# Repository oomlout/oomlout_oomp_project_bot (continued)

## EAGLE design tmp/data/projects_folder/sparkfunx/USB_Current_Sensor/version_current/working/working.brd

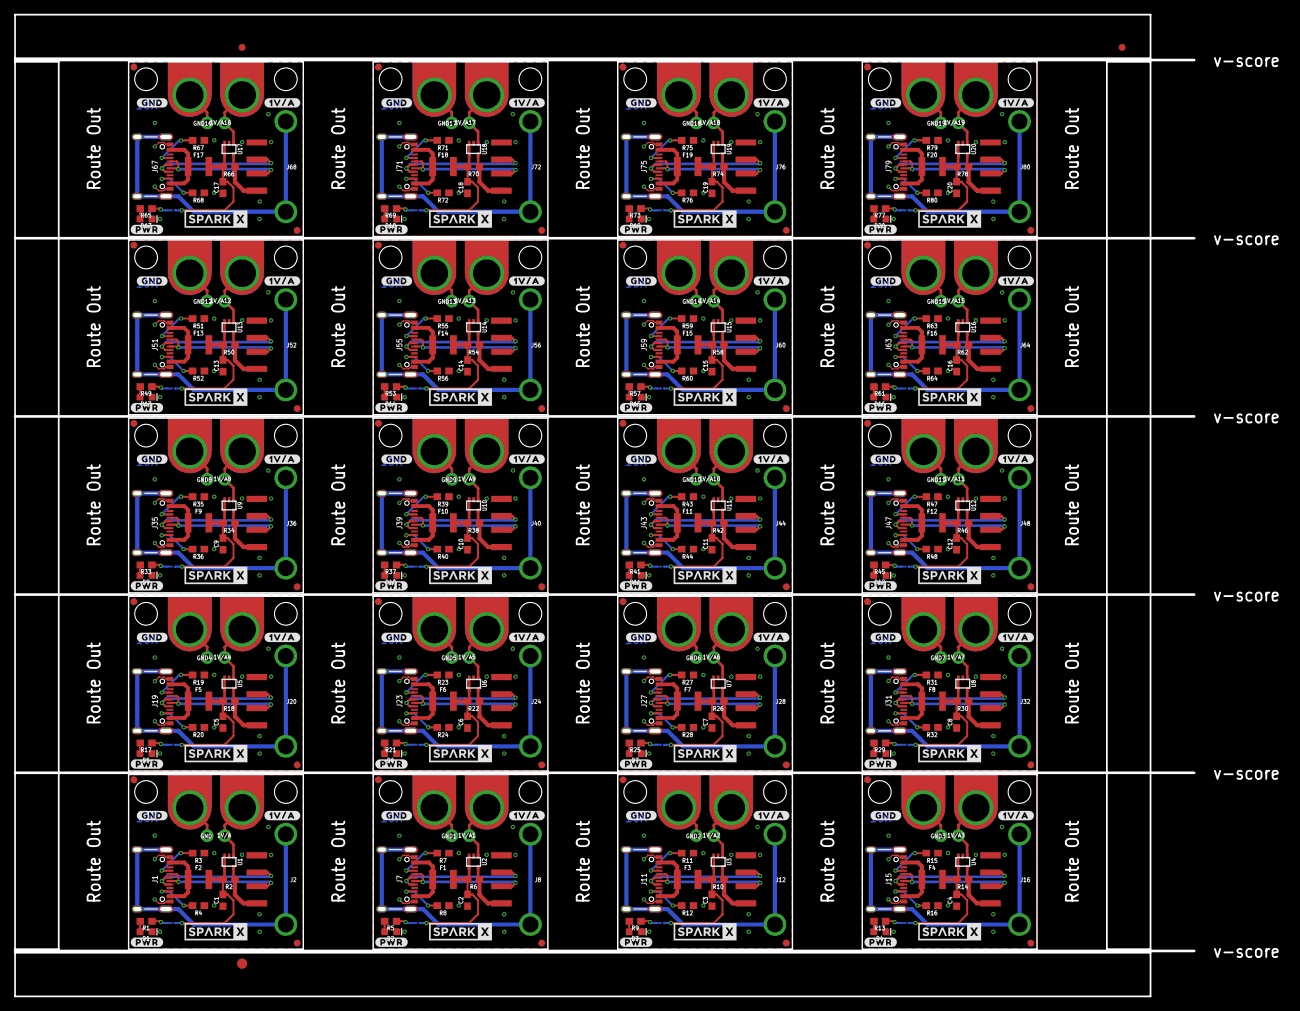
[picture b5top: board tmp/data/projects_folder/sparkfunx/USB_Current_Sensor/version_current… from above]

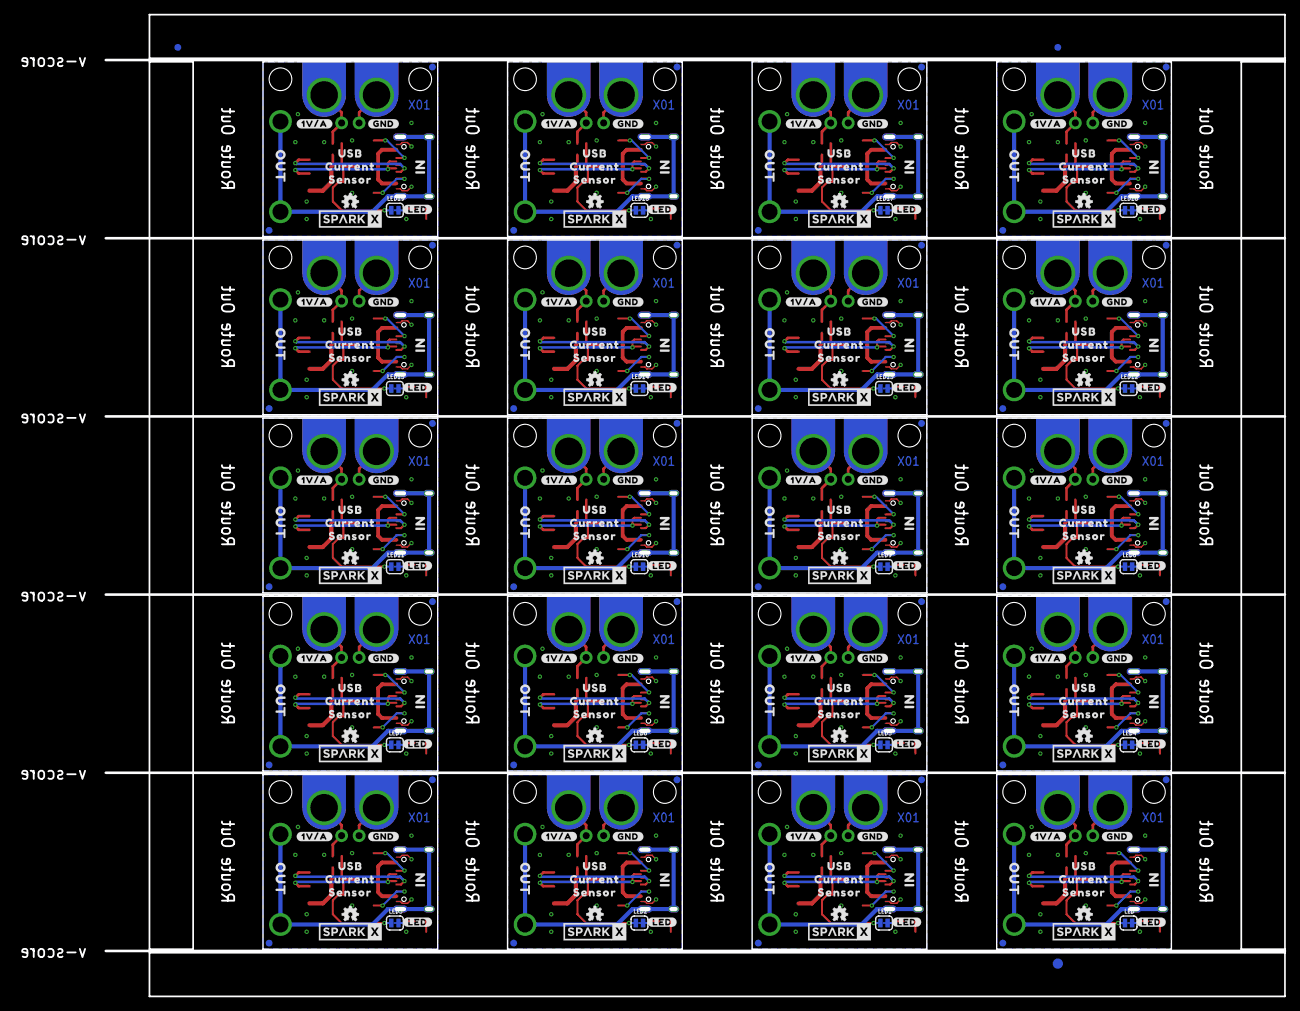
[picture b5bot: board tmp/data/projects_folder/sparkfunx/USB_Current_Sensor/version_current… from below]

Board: 2 copper layers, 171.4 x 142.7 mm, 706 parts (263 on the bottom side), 240 nets.

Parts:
1V/A, 1V/A1, 1V/A2, 1V/A3, 1V/A4, 1V/A5, 1V/A6, 1V/A7, 1V/A8, 1V/A9, 1V/A10, 1V/A11, 1V/A12, 1V/A13, 1V/A14, 1V/A15, 1V/A16, 1V/A17, 1V/A18, 1V/A19: 1X01_NO_SILK
C1, C2, C3, C4, C5, C6, C7, C8, C9, C10, C11, C12, C13, C14, C15, C16, C17, C18, C19, C20: 0.1uF; 0603
D1, D2, D3, D4, D5, D6, D7, D8, D9, D10, D11, D12, D13, D14, D15, D16, D17, D18, D19, D20: RED; LED-0603
E$1, E$2, E$3, E$4: FIDUCIAL-1X2
E$5, E$6: FIDUCIAL-1.5X3
F1, F2, F3, F4, F5, F6, F7, F8, F9, F10, F11, F12, F13, F14, F15, F16, F17, F18, F19, F20: 6V/2A; 1210
GND, GND1, GND2, GND3, GND4, GND5, GND6, GND7, GND8, GND9, GND10, GND11, GND12, GND13, GND14, GND15, GND16, GND17, GND18, GND19: 1X01_NO_SILK
J1, J7, J11, J15, J19, J23, J27, J31, J35, J39, J43, J47, J51, J55, J59, J63, J67, J71, J75, J79: USB-C-16P_4LAYER-PADS
J2, J8, J12, J16, J20, J24, J28, J32, J36, J40, J44, J48, J52, J56, J60, J64, J68, J72, J76, J80: USB_A_FEMALE; USB-A-S-NOSILK-FEMALE
J3, J4, J5, J6, J9, J10, J13, J14, J17, J18, J21, J22, J25, J26, J29, J30, J33, J34, J37, J38, J41, J42, J45, J46, J49, J50, J53, J54, J57, J58, J61, J62, J65, J66, J69, J70, J73, J74, J77, J78: TAB_GATOR_MINI
JP1, JP2, JP5, JP6, JP9, JP10, JP11, JP12, JP15, JP16, JP17, JP18, JP21, JP22, JP23, JP24, JP27, JP28, JP29, JP30, JP33, JP34, JP35, JP36, JP39, JP40, JP41, JP42, JP45, JP46, JP47, JP48, JP51, JP52, JP53, JP54, JP57, JP58, JP59, JP60, JP63, JP64, JP65, JP66, JP69, JP70, JP71, JP72, JP75, JP76, JP77, JP78, JP81, JP82, JP83, JP84, JP87, JP88, JP89, JP90, JP93, JP94, JP95, JP96, JP99, JP100, JP101, JP102, JP105, JP106, JP107, JP108, JP111, JP112, JP113, JP114, JP117, JP118, JP119, JP120: FIDUCIAL1X2; FIDUCIAL-1X2
JP3, JP4, JP7, JP8, JP13, JP14, JP19, JP20, JP25, JP26, JP31, JP32, JP37, JP38, JP43, JP44, JP49, JP50, JP55, JP56, JP61, JP62, JP67, JP68, JP73, JP74, JP79, JP80, JP85, JP86, JP91, JP92, JP97, JP98, JP103, JP104, JP109, JP110, JP115, JP116: STAND-OFF
LED, LED1, LED2, LED3, LED4, LED5, LED6, LED7, LED8, LED9, LED10, LED11, LED12, LED13, LED14, LED15, LED16, LED17, LED18, LED19: SMT-JUMPER_2_NC_TRACE_SILK
LOGO1, LOGO2, LOGO3, LOGO4, LOGO5, LOGO6, LOGO7, LOGO8, LOGO9, LOGO10, LOGO11, LOGO12, LOGO13, LOGO14, LOGO15, LOGO16, LOGO17, LOGO18, LOGO19, LOGO20: OSHW-LOGOMINI; OSHW-LOGO-MINI
R1, R5, R9, R13, R17, R21, R25, R29, R33, R37, R41, R45, R49, R53, R57, R61, R65, R69, R73, R77: 2.2k; 0603
R2, R6, R10, R14, R18, R22, R26, R30, R34, R38, R42, R46, R50, R54, R58, R62, R66, R70, R74, R78: 0.05; 0603
R3, R4, R7, R8, R11, R12, R15, R16, R19, R20, R23, R24, R27, R28, R31, R32, R35, R36, R39, R40, R43, R44, R47, R48, R51, R52, R55, R56, R59, R60, R63, R64, R67, R68, R71, R72, R75, R76, R79, R80: 5.1k; 0603
U1, U2, U3, U4, U5, U6, U7, U8, U9, U10, U11, U12, U13, U14, U15, U16, U17, U18, U19, U20: INA290A1(20V/V); SC70
U$1, U$2, U$12, U$17, U$27, U$30, U$40, U$43, U$53, U$56, U$66, U$69, U$79, U$82, U$92, U$95, U$105, U$108, U$118, U$121, U$131, U$134, U$144, U$147, U$157, U$160, U$170, U$173, U$183, U$186, U$196, U$199, U$209, U$212, U$222, U$225, U$235, U$238, U$248, U$251: SPARKX-LOGO4; SPARKX-MEDIUM
U$3, U$4, U$18, U$19, U$31, U$32, U$44, U$45, U$57, U$58, U$70, U$71, U$83, U$84, U$96, U$97, U$109, U$110, U$122, U$123, U$135, U$136, U$148, U$149, U$161, U$162, U$174, U$175, U$187, U$188, U$200, U$201, U$213, U$214, U$226, U$227, U$239, U$240, U$252, U$253: #GND#0
U$5, U$6, U$20, U$21, U$33, U$34, U$46, U$47, U$59, U$60, U$72, U$73, U$85, U$86, U$98, U$99, U$111, U$112, U$124, U$125, U$137, U$138, U$150, U$151, U$163, U$164, U$176, U$177, U$189, U$190, U$202, U$203, U$215, U$216, U$228, U$229, U$241, U$242, U$254, U$255: #1V#A#0
U$7, U$22, U$35, U$48, U$61, U$74, U$87, U$100, U$113, U$126, U$139, U$152, U$165, U$178, U$191, U$204, U$217, U$230, U$243, U$256: USB0
U$8, U$23, U$36, U$49, U$62, U$75, U$88, U$101, U$114, U$127, U$140, U$153, U$166, U$179, U$192, U$205, U$218, U$231, U$244, U$257: CURRENT0
U$9, U$24, U$37, U$50, U$63, U$76, U$89, U$102, U$115, U$128, U$141, U$154, U$167, U$180, U$193, U$206, U$219, U$232, U$245, U$258: SENSOR0
U$10, U$25, U$38, U$51, U$64, U$77, U$90, U$103, U$116, U$129, U$142, U$155, U$168, U$181, U$194, U$207, U$220, U$233, U$246, U$259: IN0
U$11, U$26, U$39, U$52, U$65, U$78, U$91, U$104, U$117, U$130, U$143, U$156, U$169, U$182, U$195, U$208, U$221, U$234, U$247, U$260: OUT0
U$13, U$15, U$28, U$41, U$54, U$67, U$80, U$93, U$106, U$119, U$132, U$145, U$158, U$171, U$184, U$197, U$210, U$223, U$236, U$249: #PWR#0
U$14, U$16, U$29, U$42, U$55, U$68, U$81, U$94, U$107, U$120, U$133, U$146, U$159, U$172, U$185, U$198, U$211, U$224, U$237, U$250: #LED#0

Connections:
1V/A: 1V/A.1, J3.P1, U1.1
1V/A1: 1V/A1.1, J5.P1, U2.1
1V/A2: 1V/A2.1, J9.P1, U3.1
1V/A3: 1V/A3.1, J13.P1, U4.1
1V/A4: 1V/A4.1, J17.P1, U5.1
1V/A5: 1V/A5.1, J21.P1, U6.1
1V/A6: 1V/A6.1, J25.P1, U7.1
1V/A7: 1V/A7.1, J29.P1, U8.1
1V/A8: 1V/A8.1, J33.P1, U9.1
1V/A9: 1V/A9.1, J37.P1, U10.1
1V/A10: 1V/A10.1, J41.P1, U11.1
1V/A11: 1V/A11.1, J45.P1, U12.1
1V/A12: 1V/A12.1, J49.P1, U13.1
1V/A13: 1V/A13.1, J53.P1, U14.1
1V/A14: 1V/A14.1, J57.P1, U15.1
1V/A15: 1V/A15.1, J61.P1, U16.1
1V/A16: 1V/A16.1, J65.P1, U17.1
1V/A17: 1V/A17.1, J69.P1, U18.1
1V/A18: 1V/A18.1, J73.P1, U19.1
1V/A19: 1V/A19.1, J77.P1, U20.1
5V: C1.1, F2.2, LED.2, R2.2, U1.3, U1.4
5V1: C2.1, F1.2, LED1.2, R6.2, U2.3, U2.4
5V2: C3.1, F3.2, LED2.2, R10.2, U3.3, U3.4
5V3: C4.1, F4.2, LED3.2, R14.2, U4.3, U4.4
5V4: C5.1, F5.2, LED4.2, R18.2, U5.3, U5.4
5V5: C6.1, F6.2, LED5.2, R22.2, U6.3, U6.4
5V6: C7.1, F7.2, LED6.2, R26.2, U7.3, U7.4
5V7: C8.1, F8.2, LED7.2, R30.2, U8.3, U8.4
5V8: C9.1, F9.2, LED8.2, R34.2, U9.3, U9.4
5V9: C10.1, F10.2, LED9.2, R38.2, U10.3, U10.4
5V10: C11.1, F11.2, LED10.2, R42.2, U11.3, U11.4
5V11: C12.1, F12.2, LED11.2, R46.2, U12.3, U12.4
5V12: C13.1, F13.2, LED12.2, R50.2, U13.3, U13.4
5V13: C14.1, F14.2, LED13.2, R54.2, U14.3, U14.4
5V14: C15.1, F15.2, LED14.2, R58.2, U15.3, U15.4
5V15: C16.1, F16.2, LED15.2, R62.2, U16.3, U16.4
5V16: C17.1, F17.2, LED16.2, R66.2, U17.3, U17.4
5V17: C18.1, F18.2, LED17.2, R70.2, U18.3, U18.4
5V18: C19.1, F19.2, LED18.2, R74.2, U19.3, U19.4
5V19: C20.1, F20.2, LED19.2, R78.2, U20.3, U20.4
GND: C1.2, D1.C, GND.1, J1.GND, J1.GND2, J2.GND, J4.P1, R3.1, R4.1, U1.2
GND1: C2.2, D2.C, GND1.1, J6.P1, J7.GND, J7.GND2, J8.GND, R7.1, R8.1, U2.2
GND2: C3.2, D3.C, GND2.1, J10.P1, J11.GND, J11.GND2, J12.GND, R11.1, R12.1, U3.2
GND3: C4.2, D4.C, GND3.1, J14.P1, J15.GND, J15.GND2, J16.GND, R15.1, R16.1, U4.2
GND4: C5.2, D5.C, GND4.1, J18.P1, J19.GND, J19.GND2, J20.GND, R19.1, R20.1, U5.2
GND5: C6.2, D6.C, GND5.1, J22.P1, J23.GND, J23.GND2, J24.GND, R23.1, R24.1, U6.2
GND6: C7.2, D7.C, GND6.1, J26.P1, J27.GND, J27.GND2, J28.GND, R27.1, R28.1, U7.2
GND7: C8.2, D8.C, GND7.1, J30.P1, J31.GND, J31.GND2, J32.GND, R31.1, R32.1, U8.2
GND8: C9.2, D9.C, GND8.1, J34.P1, J35.GND, J35.GND2, J36.GND, R35.1, R36.1, U9.2
GND9: C10.2, D10.C, GND9.1, J38.P1, J39.GND, J39.GND2, J40.GND, R39.1, R40.1, U10.2
GND10: C11.2, D11.C, GND10.1, J42.P1, J43.GND, J43.GND2, J44.GND, R43.1, R44.1, U11.2
GND11: C12.2, D12.C, GND11.1, J46.P1, J47.GND, J47.GND2, J48.GND, R47.1, R48.1, U12.2
GND12: C13.2, D13.C, GND12.1, J50.P1, J51.GND, J51.GND2, J52.GND, R51.1, R52.1, U13.2
GND13: C14.2, D14.C, GND13.1, J54.P1, J55.GND, J55.GND2, J56.GND, R55.1, R56.1, U14.2
GND14: C15.2, D15.C, GND14.1, J58.P1, J59.GND, J59.GND2, J60.GND, R59.1, R60.1, U15.2
GND15: C16.2, D16.C, GND15.1, J62.P1, J63.GND, J63.GND2, J64.GND, R63.1, R64.1, U16.2
GND16: C17.2, D17.C, GND16.1, J66.P1, J67.GND, J67.GND2, J68.GND, R67.1, R68.1, U17.2
GND17: C18.2, D18.C, GND17.1, J70.P1, J71.GND, J71.GND2, J72.GND, R71.1, R72.1, U18.2
GND18: C19.2, D19.C, GND18.1, J74.P1, J75.GND, J75.GND2, J76.GND, R75.1, R76.1, U19.2
GND19: C20.2, D20.C, GND19.1, J78.P1, J79.GND, J79.GND2, J80.GND, R79.1, R80.1, U20.2
unnamed: D2.A, R5.1
unnamed: LED1.1, R5.2
unnamed: D1.A, R1.1
unnamed: LED.1, R1.2
unnamed: J7.A5, R7.2
unnamed: J7.B5, R8.2
unnamed: F1.1, J7.VBUS1, J7.VBUS2
unnamed: D3.A, R9.1
unnamed: LED2.1, R9.2
unnamed: J1.A5, R3.2
unnamed: J1.B5, R4.2
unnamed: J11.A5, R11.2
unnamed: J11.B5, R12.2
unnamed: F3.1, J11.VBUS1, J11.VBUS2
unnamed: D4.A, R13.1
unnamed: LED3.1, R13.2
unnamed: J15.A5, R15.2
unnamed: J15.B5, R16.2
unnamed: F2.1, J1.VBUS1, J1.VBUS2
unnamed: F4.1, J15.VBUS1, J15.VBUS2
unnamed: D5.A, R17.1
unnamed: LED4.1, R17.2
unnamed: J19.A5, R19.2
unnamed: J19.B5, R20.2
unnamed: F5.1, J19.VBUS1, J19.VBUS2
unnamed: D6.A, R21.1
unnamed: LED5.1, R21.2
unnamed: J23.A5, R23.2
unnamed: J23.B5, R24.2
unnamed: F6.1, J23.VBUS1, J23.VBUS2
unnamed: D7.A, R25.1
unnamed: LED6.1, R25.2
unnamed: J27.A5, R27.2
unnamed: J27.B5, R28.2
unnamed: F7.1, J27.VBUS1, J27.VBUS2
unnamed: D8.A, R29.1
unnamed: LED7.1, R29.2
unnamed: J31.A5, R31.2
unnamed: J31.B5, R32.2
unnamed: F8.1, J31.VBUS1, J31.VBUS2
unnamed: D9.A, R33.1
unnamed: LED8.1, R33.2
unnamed: J35.A5, R35.2
unnamed: J35.B5, R36.2
unnamed: F9.1, J35.VBUS1, J35.VBUS2
unnamed: D10.A, R37.1
unnamed: LED9.1, R37.2
unnamed: J39.A5, R39.2
unnamed: J39.B5, R40.2
unnamed: F10.1, J39.VBUS1, J39.VBUS2
unnamed: D11.A, R41.1
unnamed: LED10.1, R41.2
unnamed: J43.A5, R43.2
unnamed: J43.B5, R44.2
unnamed: F11.1, J43.VBUS1, J43.VBUS2
unnamed: D12.A, R45.1
unnamed: LED11.1, R45.2
unnamed: J47.A5, R47.2
unnamed: J47.B5, R48.2
unnamed: F12.1, J47.VBUS1, J47.VBUS2
unnamed: D13.A, R49.1
unnamed: LED12.1, R49.2
unnamed: J51.A5, R51.2
unnamed: J51.B5, R52.2
unnamed: F13.1, J51.VBUS1, J51.VBUS2
unnamed: D14.A, R53.1
unnamed: LED13.1, R53.2
unnamed: J55.A5, R55.2
unnamed: J55.B5, R56.2
unnamed: F14.1, J55.VBUS1, J55.VBUS2
unnamed: D15.A, R57.1
unnamed: LED14.1, R57.2
unnamed: J59.A5, R59.2
unnamed: J59.B5, R60.2
unnamed: F15.1, J59.VBUS1, J59.VBUS2
unnamed: D16.A, R61.1
unnamed: LED15.1, R61.2
unnamed: J63.A5, R63.2
unnamed: J63.B5, R64.2
unnamed: F16.1, J63.VBUS1, J63.VBUS2
unnamed: D17.A, R65.1
unnamed: LED16.1, R65.2
unnamed: J67.A5, R67.2
unnamed: J67.B5, R68.2
unnamed: F17.1, J67.VBUS1, J67.VBUS2
unnamed: D18.A, R69.1
unnamed: LED17.1, R69.2
unnamed: J71.A5, R71.2
unnamed: J71.B5, R72.2
unnamed: F18.1, J71.VBUS1, J71.VBUS2
unnamed: D19.A, R73.1
unnamed: LED18.1, R73.2
unnamed: J75.A5, R75.2
unnamed: J75.B5, R76.2
unnamed: F19.1, J75.VBUS1, J75.VBUS2
unnamed: D20.A, R77.1
unnamed: LED19.1, R77.2
unnamed: J79.A5, R79.2
unnamed: J79.B5, R80.2
unnamed: F20.1, J79.VBUS1, J79.VBUS2
SHLD: J1.SHLD1, J1.SHLD2, J1.SHLD3, J1.SHLD4, J2.SHLD1, J2.SHLD2
SHLD1: J7.SHLD1, J7.SHLD2, J7.SHLD3, J7.SHLD4, J8.SHLD1, J8.SHLD2
SHLD2: J11.SHLD1, J11.SHLD2, J11.SHLD3, J11.SHLD4, J12.SHLD1, J12.SHLD2
SHLD3: J15.SHLD1, J15.SHLD2, J15.SHLD3, J15.SHLD4, J16.SHLD1, J16.SHLD2
SHLD4: J19.SHLD1, J19.SHLD2, J19.SHLD3, J19.SHLD4, J20.SHLD1, J20.SHLD2
SHLD5: J23.SHLD1, J23.SHLD2, J23.SHLD3, J23.SHLD4, J24.SHLD1, J24.SHLD2
SHLD6: J27.SHLD1, J27.SHLD2, J27.SHLD3, J27.SHLD4, J28.SHLD1, J28.SHLD2
SHLD7: J31.SHLD1, J31.SHLD2, J31.SHLD3, J31.SHLD4, J32.SHLD1, J32.SHLD2
SHLD8: J35.SHLD1, J35.SHLD2, J35.SHLD3, J35.SHLD4, J36.SHLD1, J36.SHLD2
SHLD9: J39.SHLD1, J39.SHLD2, J39.SHLD3, J39.SHLD4, J40.SHLD1, J40.SHLD2
SHLD10: J43.SHLD1, J43.SHLD2, J43.SHLD3, J43.SHLD4, J44.SHLD1, J44.SHLD2
SHLD11: J47.SHLD1, J47.SHLD2, J47.SHLD3, J47.SHLD4, J48.SHLD1, J48.SHLD2
SHLD12: J51.SHLD1, J51.SHLD2, J51.SHLD3, J51.SHLD4, J52.SHLD1, J52.SHLD2
SHLD13: J55.SHLD1, J55.SHLD2, J55.SHLD3, J55.SHLD4, J56.SHLD1, J56.SHLD2
SHLD14: J59.SHLD1, J59.SHLD2, J59.SHLD3, J59.SHLD4, J60.SHLD1, J60.SHLD2
SHLD15: J63.SHLD1, J63.SHLD2, J63.SHLD3, J63.SHLD4, J64.SHLD1, J64.SHLD2
SHLD16: J67.SHLD1, J67.SHLD2, J67.SHLD3, J67.SHLD4, J68.SHLD1, J68.SHLD2
SHLD17: J71.SHLD1, J71.SHLD2, J71.SHLD3, J71.SHLD4, J72.SHLD1, J72.SHLD2
SHLD18: J75.SHLD1, J75.SHLD2, J75.SHLD3, J75.SHLD4, J76.SHLD1, J76.SHLD2
SHLD19: J79.SHLD1, J79.SHLD2, J79.SHLD3, J79.SHLD4, J80.SHLD1, J80.SHLD2
USB_D+: J1.A6, J1.B6, J2.D+
USB_D+1: J7.A6, J7.B6, J8.D+
USB_D+2: J11.A6, J11.B6, J12.D+
USB_D+3: J15.A6, J15.B6, J16.D+
USB_D+4: J19.A6, J19.B6, J20.D+
USB_D+5: J23.A6, J23.B6, J24.D+
USB_D+6: J27.A6, J27.B6, J28.D+
USB_D+7: J31.A6, J31.B6, J32.D+
USB_D+8: J35.A6, J35.B6, J36.D+
USB_D+9: J39.A6, J39.B6, J40.D+
USB_D+10: J43.A6, J43.B6, J44.D+
USB_D+11: J47.A6, J47.B6, J48.D+
USB_D+12: J51.A6, J51.B6, J52.D+
USB_D+13: J55.A6, J55.B6, J56.D+
USB_D+14: J59.A6, J59.B6, J60.D+
USB_D+15: J63.A6, J63.B6, J64.D+
USB_D+16: J67.A6, J67.B6, J68.D+
USB_D+17: J71.A6, J71.B6, J72.D+
USB_D+18: J75.A6, J75.B6, J76.D+
USB_D+19: J79.A6, J79.B6, J80.D+
USB_D-: J1.A7, J1.B7, J2.D-
USB_D-1: J7.A7, J7.B7, J8.D-
USB_D-2: J11.A7, J11.B7, J12.D-
USB_D-3: J15.A7, J15.B7, J16.D-
USB_D-4: J19.A7, J19.B7, J20.D-
USB_D-5: J23.A7, J23.B7, J24.D-
USB_D-6: J27.A7, J27.B7, J28.D-
USB_D-7: J31.A7, J31.B7, J32.D-
USB_D-8: J35.A7, J35.B7, J36.D-
USB_D-9: J39.A7, J39.B7, J40.D-
USB_D-10: J43.A7, J43.B7, J44.D-
USB_D-11: J47.A7, J47.B7, J48.D-
USB_D-12: J51.A7, J51.B7, J52.D-
USB_D-13: J55.A7, J55.B7, J56.D-
USB_D-14: J59.A7, J59.B7, J60.D-
USB_D-15: J63.A7, J63.B7, J64.D-
USB_D-16: J67.A7, J67.B7, J68.D-
USB_D-17: J71.A7, J71.B7, J72.D-
USB_D-18: J75.A7, J75.B7, J76.D-
USB_D-19: J79.A7, J79.B7, J80.D-
VOUT: J2.VBUS, R2.1, U1.5
VOUT1: J8.VBUS, R6.1, U2.5
VOUT2: J12.VBUS, R10.1, U3.5
VOUT3: J16.VBUS, R14.1, U4.5
VOUT4: J20.VBUS, R18.1, U5.5
VOUT5: J24.VBUS, R22.1, U6.5
VOUT6: J28.VBUS, R26.1, U7.5
VOUT7: J32.VBUS, R30.1, U8.5
VOUT8: J36.VBUS, R34.1, U9.5
VOUT9: J40.VBUS, R38.1, U10.5
VOUT10: J44.VBUS, R42.1, U11.5
VOUT11: J48.VBUS, R46.1, U12.5
VOUT12: J52.VBUS, R50.1, U13.5
VOUT13: J56.VBUS, R54.1, U14.5
VOUT14: J60.VBUS, R58.1, U15.5
VOUT15: J64.VBUS, R62.1, U16.5
VOUT16: J68.VBUS, R66.1, U17.5
VOUT17: J72.VBUS, R70.1, U18.5
VOUT18: J76.VBUS, R74.1, U19.5
VOUT19: J80.VBUS, R78.1, U20.5
